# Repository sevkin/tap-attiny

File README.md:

# Пьезоконцевик TAP350

Для дельтапринтеров и прочих воронов

* Микроконтроллер attiny13a
* Пьеза 35мм
* Шар 8г (тяжелее 10г может не работать)

Прошивочный разъём при*ан на от**бись мгтф проводом.

Основан на схеме и прошивке https://github.com/ripinteer/tap-attiny/

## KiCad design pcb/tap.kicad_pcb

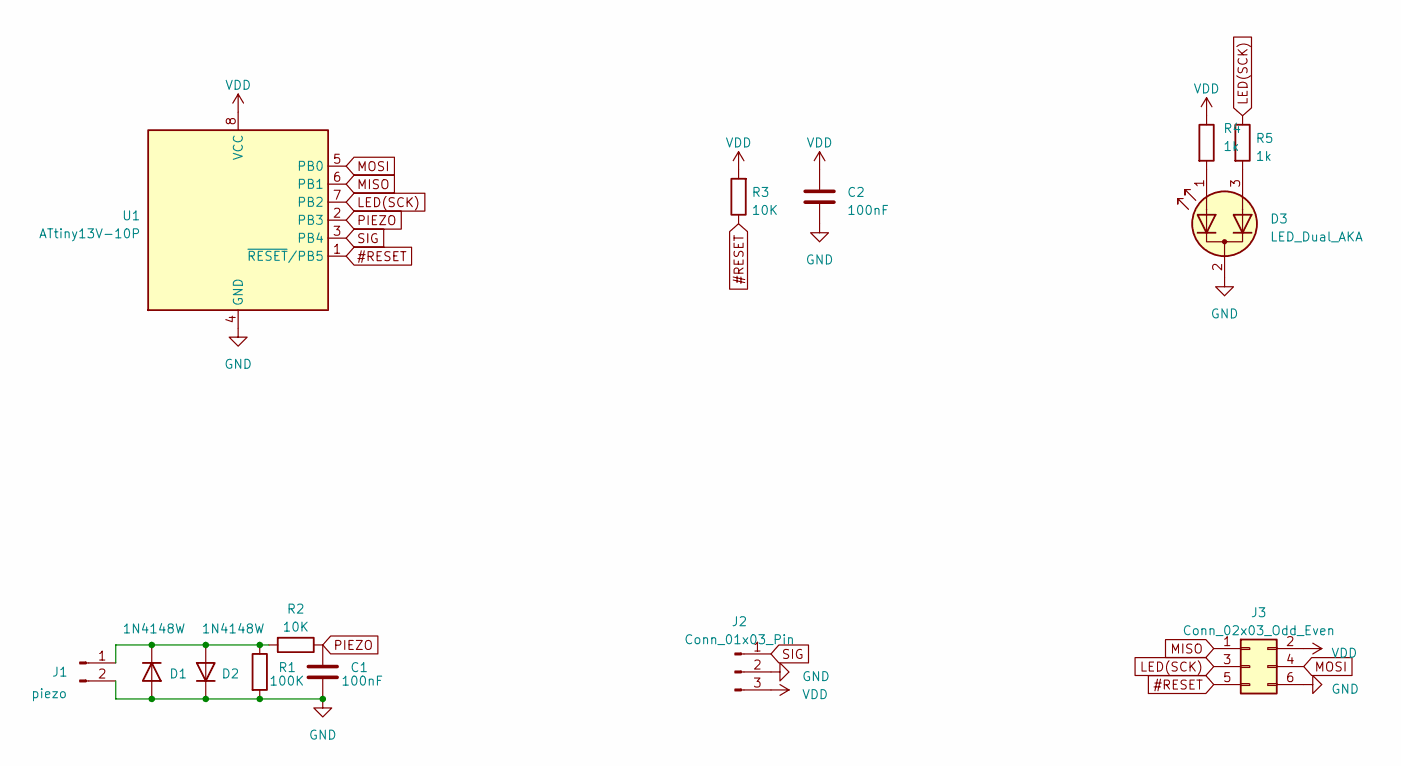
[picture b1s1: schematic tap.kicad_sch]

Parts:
C1, C2: 100nF; C_Disc_D3.4mm_W2.1mm_P2.50mm
D1, D2: 1N4148W; D_DO-35_SOD27_P2.54mm_Vertical_AnodeUp
D3: LED_Dual_AKA; LED_D3.0mm-3
J1: piezo; PinSocket_1x02_P2.54mm_Vertical
J2: Conn_01x03_Pin; JST_XH_S3B-XH-A-1_1x03_P2.50mm_Horizontal
J3: Conn_02x03_Odd_Even; PinHeader_2x03_P2.54mm_Vertical
R1: 100K; R_Axial_DIN0207_L6.3mm_D2.5mm_P2.54mm_Vertical
R2: 10K; R_Axial_DIN0207_L6.3mm_D2.5mm_P2.54mm_Vertical
R3: 10K; R_Axial_DIN0207_L6.3mm_D2.5mm_P7.62mm_Horizontal
R4, R5: 1k; R_Axial_DIN0207_L6.3mm_D2.5mm_P2.54mm_Vertical
U1: ATtiny13V-10P; DIP-8_W7.62mm

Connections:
#RESET: J3.5, R3.1, U1.1 (~RESET/PB5)
GND: C1.2, C2.2, D1.2 (A), D2.1 (K), D3.2 (K), J1.2, J2.2, J3.6, R1.2, U1.4 (GND)
LED(SCK): J3.3, R5.1, U1.7 (PB2)
MISO: J3.1, U1.6 (PB1)
MOSI: J3.4, U1.5 (PB0)
unnamed: D1.1 (K), D2.2 (A), J1.1, R1.1, R2.2
unnamed: D3.1 (A1), R4.2
unnamed: D3.3 (A2), R5.2
PIEZO: C1.1, R2.1, U1.2 (PB3)
SIG: J2.1, U1.3 (PB4)
VDD: C2.1, J2.3, J3.2, R3.2, R4.1, U1.8 (VCC)

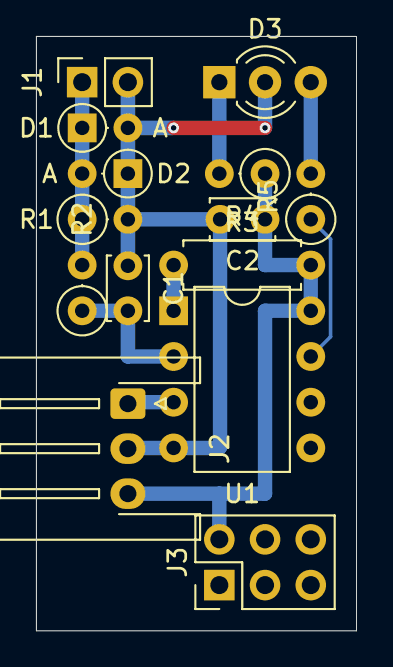
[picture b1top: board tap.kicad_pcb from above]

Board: 2 copper layers, 17.8 x 33.0 mm, 14 parts (0 on the bottom side), 11 nets.

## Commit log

2023-05-26 initial import
2023-05-29 pcb added
2023-05-29 sensivity tuned
2023-05-29 readme added
